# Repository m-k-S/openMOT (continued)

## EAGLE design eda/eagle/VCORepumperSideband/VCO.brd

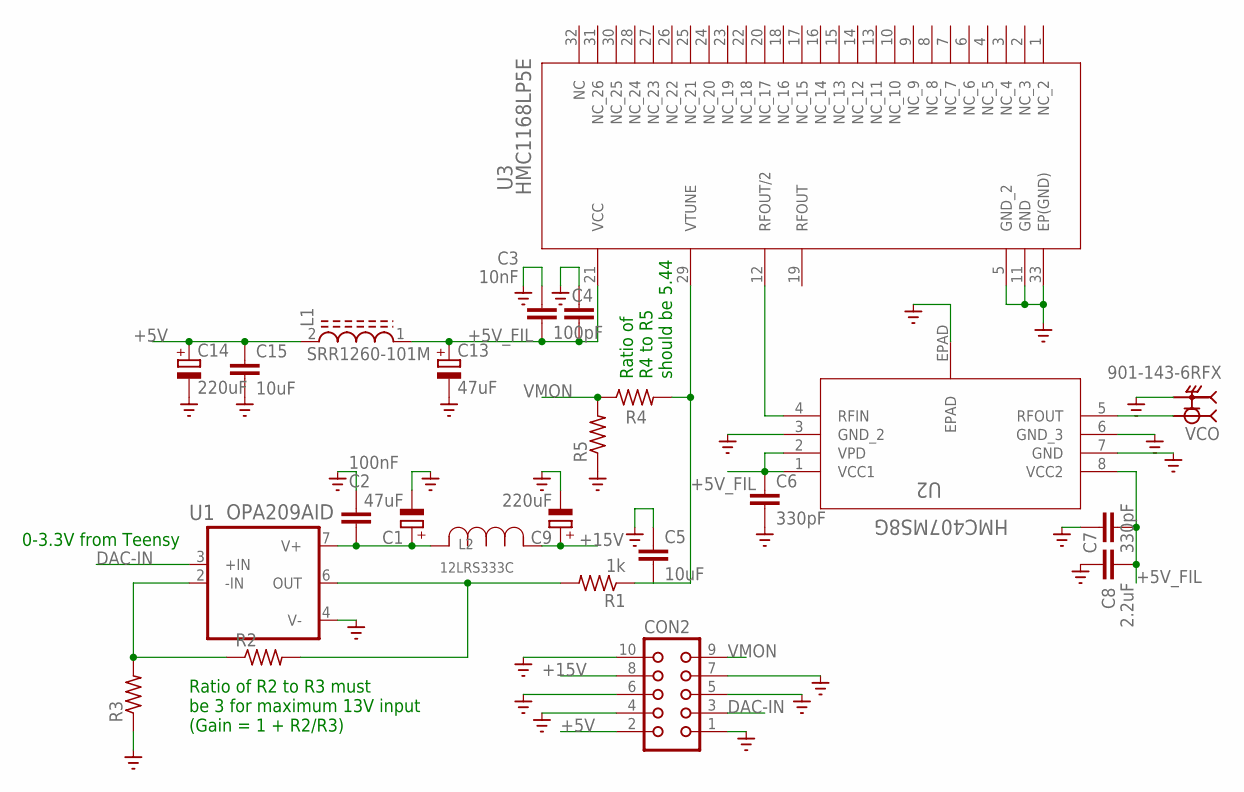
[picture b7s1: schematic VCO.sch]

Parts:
C1, C13: 47uF; 175TMP-0808
C2: 100nF; C1206
C3: 10nF; C0603
C4: 100pF; C0603
C5, C15: 10uF; C1206
C6, C7: 330pF; C0603
C8: 2.2uF; C0603
C9, C14: 220uF; E3,5-8
CON2: CON10
L1: SRR1260-101M; INDP125125X600N
L2: 12LRS333C; IND_MURATA_1200LRS_MUR
R1: 1k; R1206
R2, R3: R-US_R1206; R1206
R4, R5: R-US_R0603; R0603
U1: OPA209AID; SOIC127P599X175-8N
U2: HMC407MS8G; RH-8-1_ADI
U3: HMC1168LP5E; HCP_32_1_ADI
VCO: 901-143-6RFX; AMPHENOL_901-143-6RFX

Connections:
+5V: C14.+, C15.1, CON2.2, L1.2
+5V_FIL: C3.2, C4.2, C6.1, C7.2, C8.2, C13.+, L1.1, U2.1 (VCC1), U2.2 (VPD), U2.8 (VCC2), U3.21 (VCC)
+15V: C9.+, CON2.8, L2.1
DAC-IN: CON2.3, U1.3 (+IN)
GND: C1.-, C2.1, C3.1, C4.1, C5.1, C6.2, C7.1, C8.1, C9.-, C13.-, C14.-, C15.2, CON2.1, CON2.4, CON2.5, CON2.6, CON2.7, CON2.10, R3.1, R5.1, U1.4 (V-), U2.3 (GND_2), U2.6 (GND_3), U2.7 (GND), U2.EPAD, U3.5 (GND_2), U3.11 (GND), U3.33 (EP(GND)), VCO.S1 (2), VCO.S2 (2), VCO.S3 (2), VCO.S4 (2)
unnamed: U2.4 (RFIN), U3.12 (RFOUT/2)
unnamed: U2.5 (RFOUT), VCO.1
unnamed: C5.2, R1.1, R4.2, U3.29 (VTUNE)
unnamed: R2.1, R3.2, U1.2 (-IN)
unnamed: C1.+, C2.2, L2.3, U1.7 (V+)
unnamed: R1.2, R2.2, U1.6 (OUT)
VMON: CON2.9, R4.1, R5.2

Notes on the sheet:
Ratio of R2 to R3 must be 3 for maximum 13V input (Gain = 1 + R2/R3)
Ratio of R4 to R5 should be 5.44
0-3.3V from Teensy

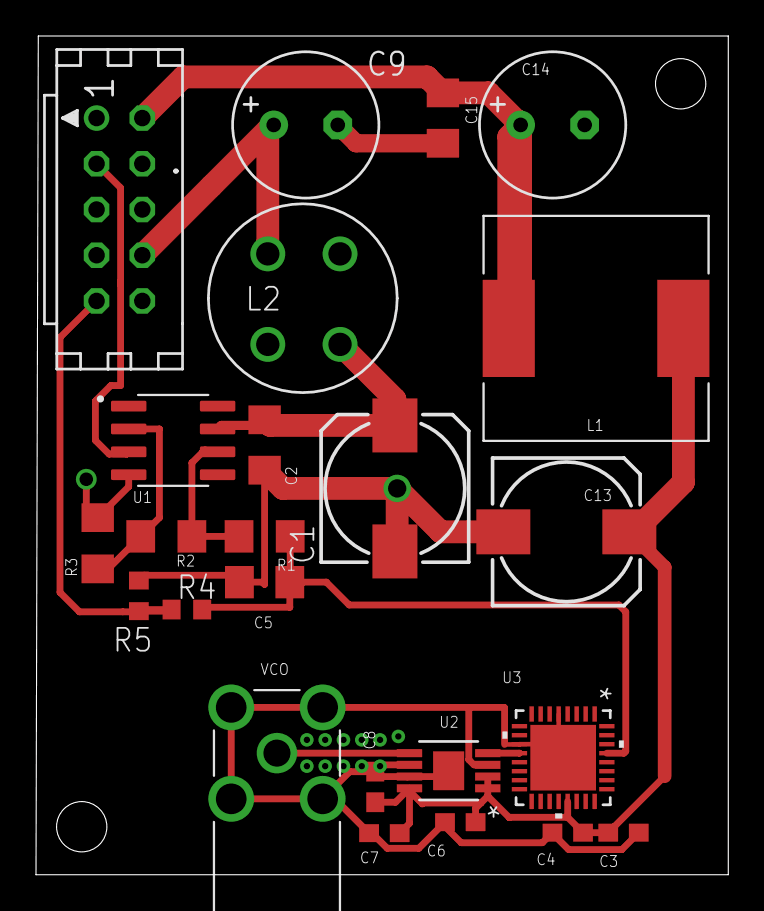
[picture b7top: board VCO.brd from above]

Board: 2 copper layers, 38.5 x 46.6 mm, 24 parts (0 on the bottom side), 12 nets.

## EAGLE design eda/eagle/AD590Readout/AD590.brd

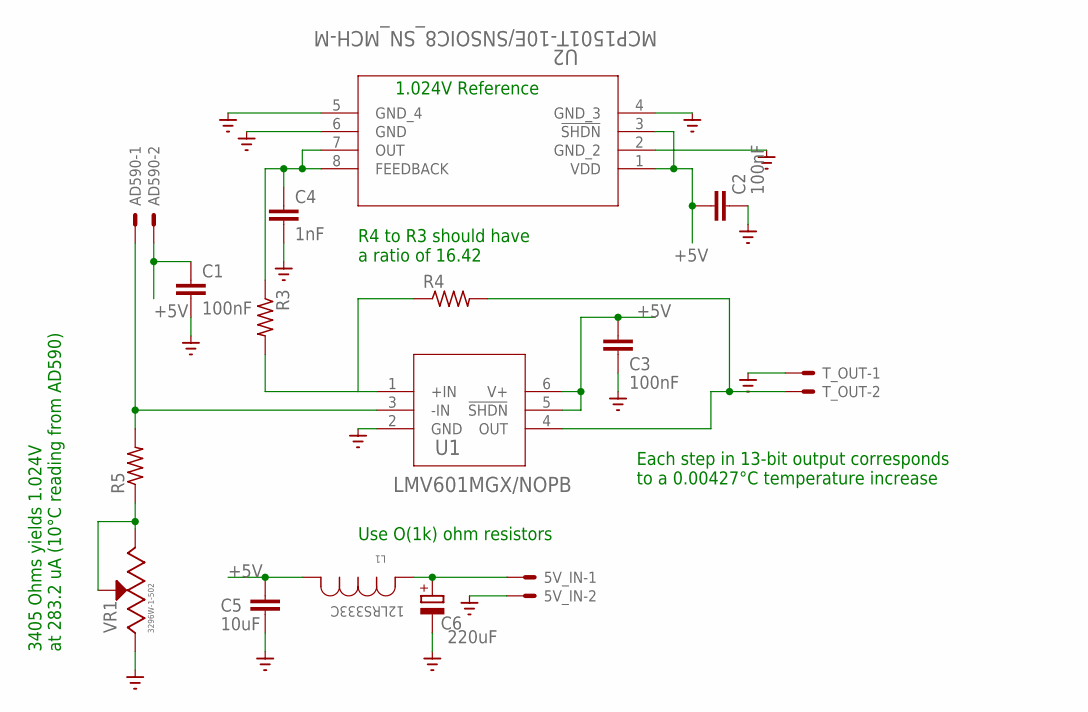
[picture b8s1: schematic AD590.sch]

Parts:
5V_IN: JST-XH-02-PIN-LONG-PAD; JST-XH-02-PACKAGE-LONG-PAD
AD590: JST-XH-02-PIN-LONG-PAD; JST-XH-02-PACKAGE-LONG-PAD
C1, C2, C3: 100nF; C0603
C4: 1nF; C0603
C5: 10uF; C0603
C6: 220uF; E3,5-8
L1: 12LRS333C; IND_MURATA_1200LRS_MUR
R3, R4, R5: R-US_R1206; R1206
T_OUT: JST-XH-02-PIN-LONG-PAD; JST-XH-02-PACKAGE-LONG-PAD
U1: LMV601MGX/NOPB; DCK6_TEX
U2: MCP1501T-10E/SNSOIC8_SN_MCH-M; SOIC8_SN_MCH-M
VR1: 3296W-1-502; TRIM_3296W-1-502

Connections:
+5V: AD590.2, C1.1, C2.1, C3.1, C5.1, L1.1, U1.5 (!SHDN), U1.6 (V+), U2.1 (VDD), U2.3 (!SHDN)
GND: 5V_IN.2, C1.2, C2.2, C3.2, C4.2, C5.2, C6.-, T_OUT.1, U1.2 (GND), U2.2 (GND_2), U2.4 (GND_3), U2.5 (GND_4), U2.6 (GND), VR1.1 (CCW)
unnamed: R5.1, VR1.2 (WIPER), VR1.3 (CW)
unnamed: AD590.1, R5.2, U1.3 (-IN)
unnamed: C4.1, R3.1, U2.7 (OUT), U2.8 (FEEDBACK)
unnamed: 5V_IN.1, C6.+, L1.3
unnamed: R4.2, T_OUT.2, U1.4 (OUT)
unnamed: R3.2, R4.1, U1.1 (+IN)

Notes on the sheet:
R4 to R3 should have a ratio of 16.42
3405 Ohms yields 1.024V at 283.2 uA (10°C reading from AD590)
1.024V Reference
Each step in 13-bit output corresponds to a 0.00427°C temperature increase
Use O(1k) ohm resistors

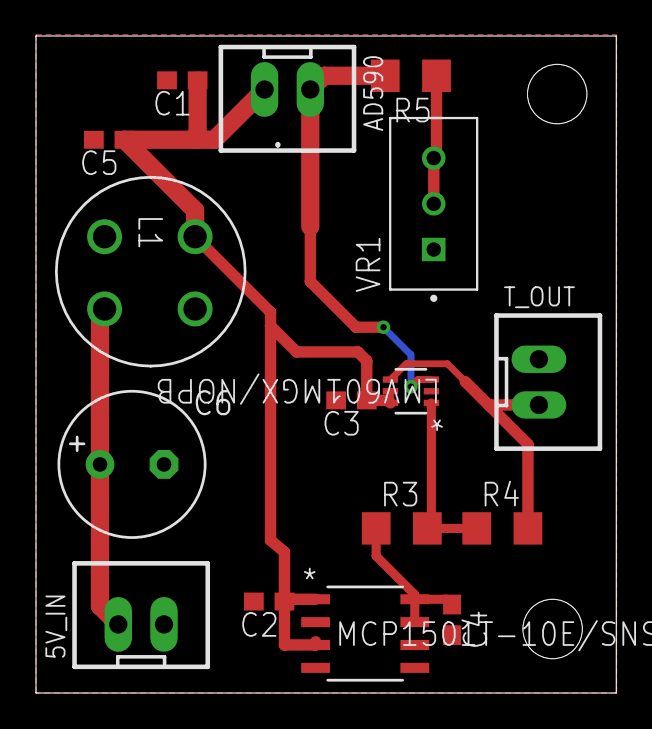
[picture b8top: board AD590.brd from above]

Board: 2 copper layers, 32.2 x 36.5 mm, 16 parts (0 on the bottom side), 8 nets.

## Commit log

2022-01-12 test commit
2022-01-12 cleaning
2022-01-20 adding EAGLE electronics files and various STEP files
2022-01-20 adding isolator component step files
